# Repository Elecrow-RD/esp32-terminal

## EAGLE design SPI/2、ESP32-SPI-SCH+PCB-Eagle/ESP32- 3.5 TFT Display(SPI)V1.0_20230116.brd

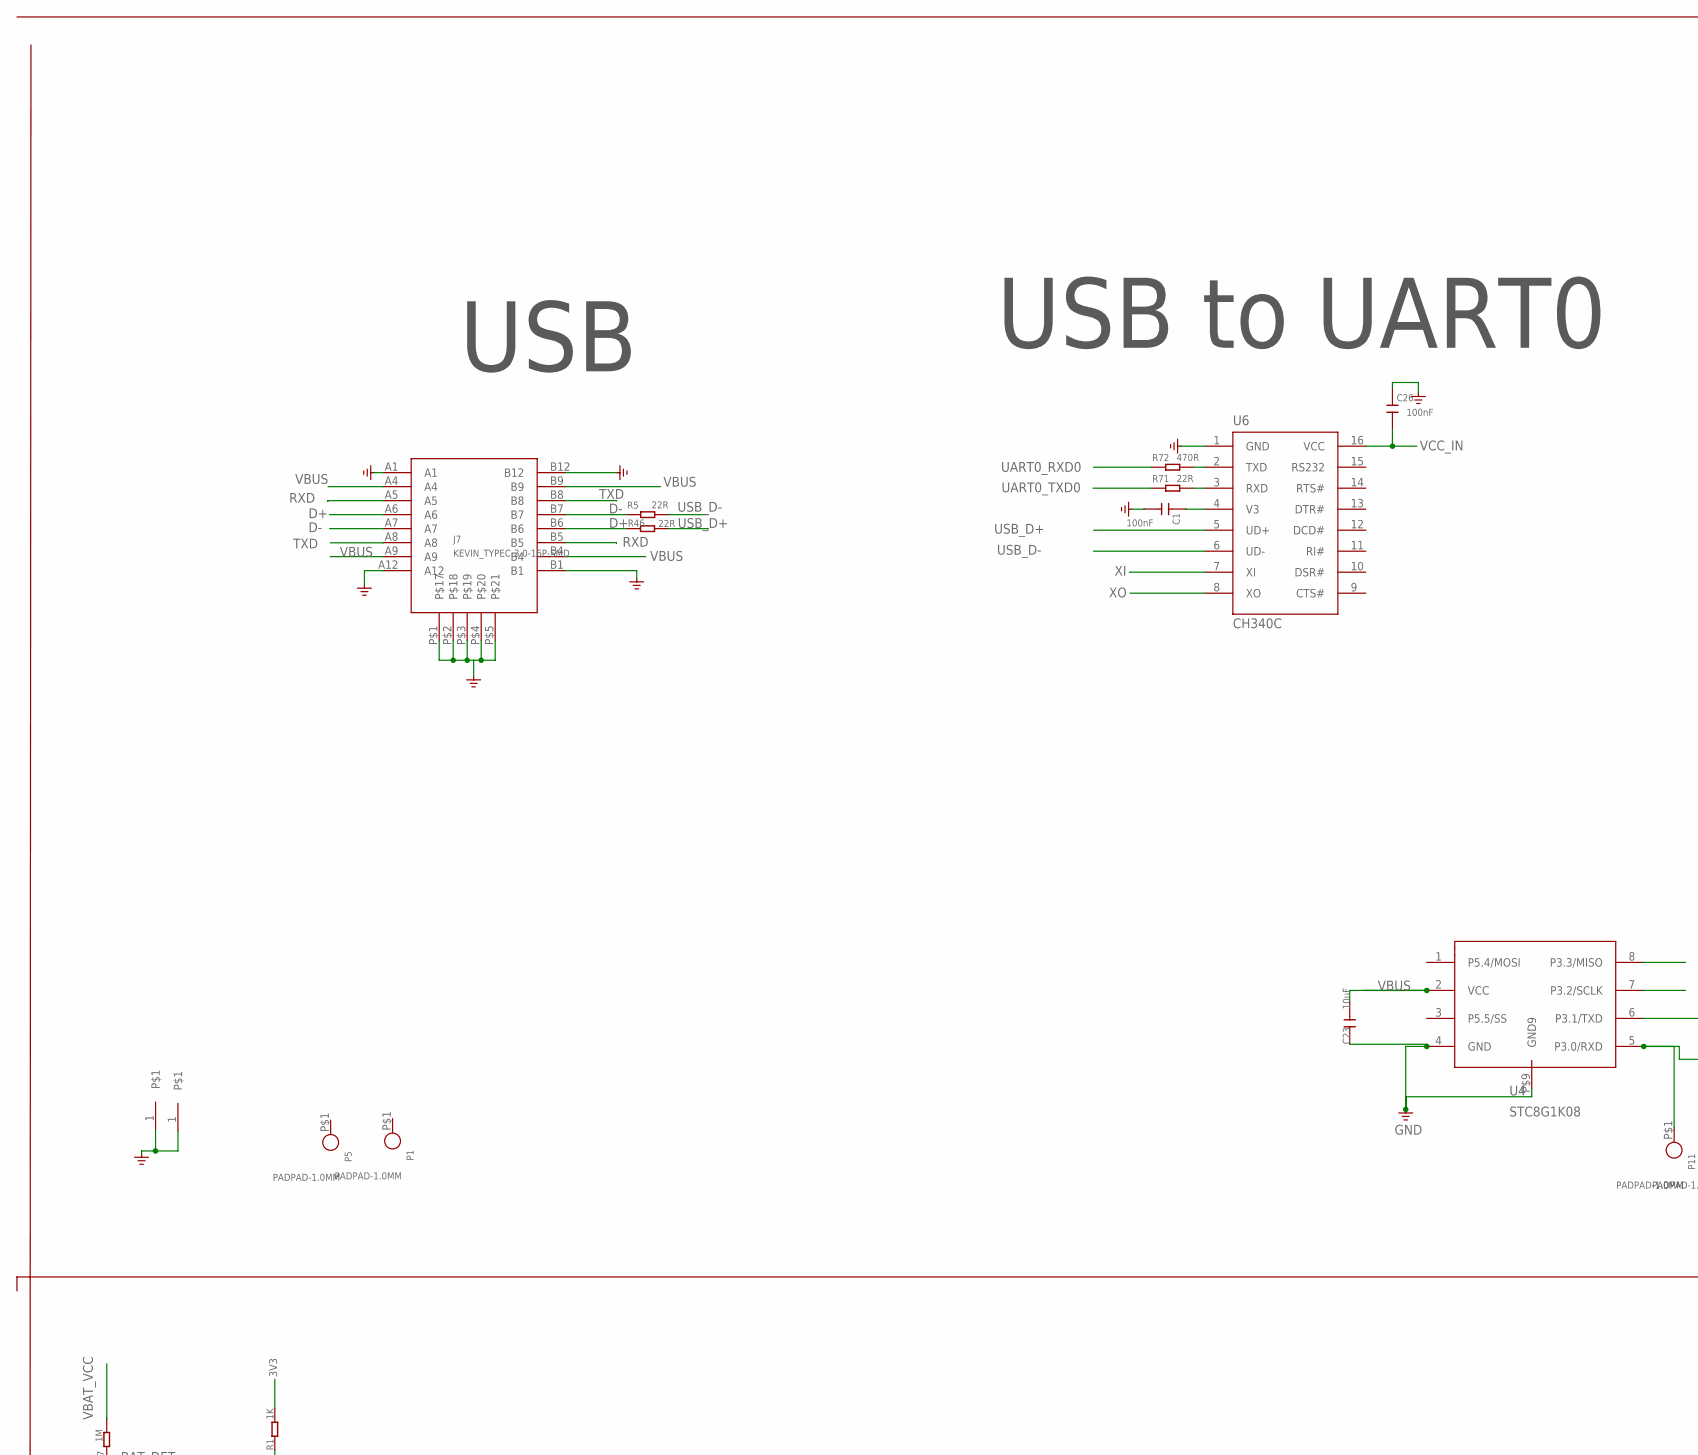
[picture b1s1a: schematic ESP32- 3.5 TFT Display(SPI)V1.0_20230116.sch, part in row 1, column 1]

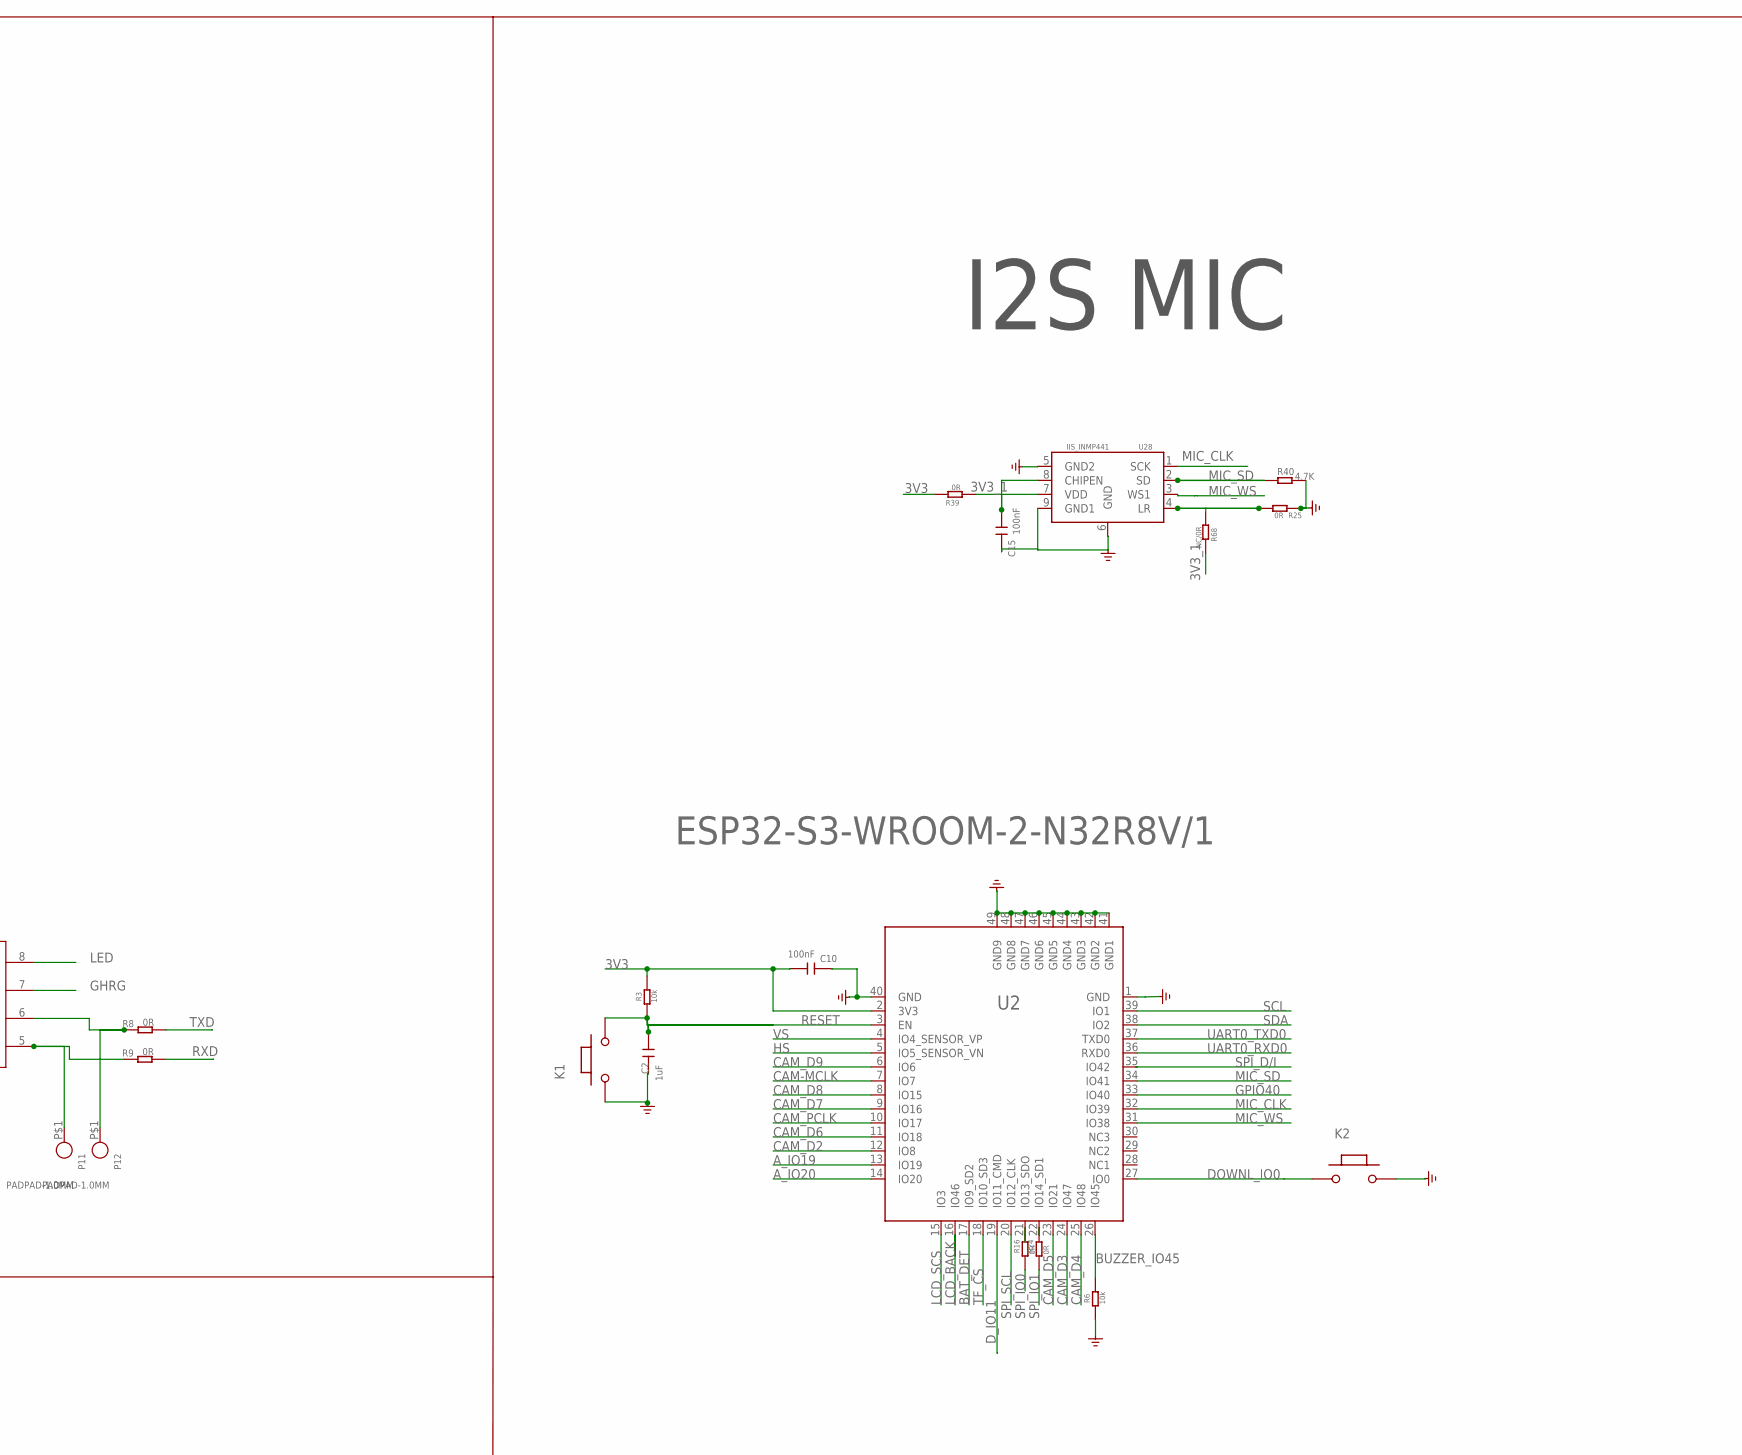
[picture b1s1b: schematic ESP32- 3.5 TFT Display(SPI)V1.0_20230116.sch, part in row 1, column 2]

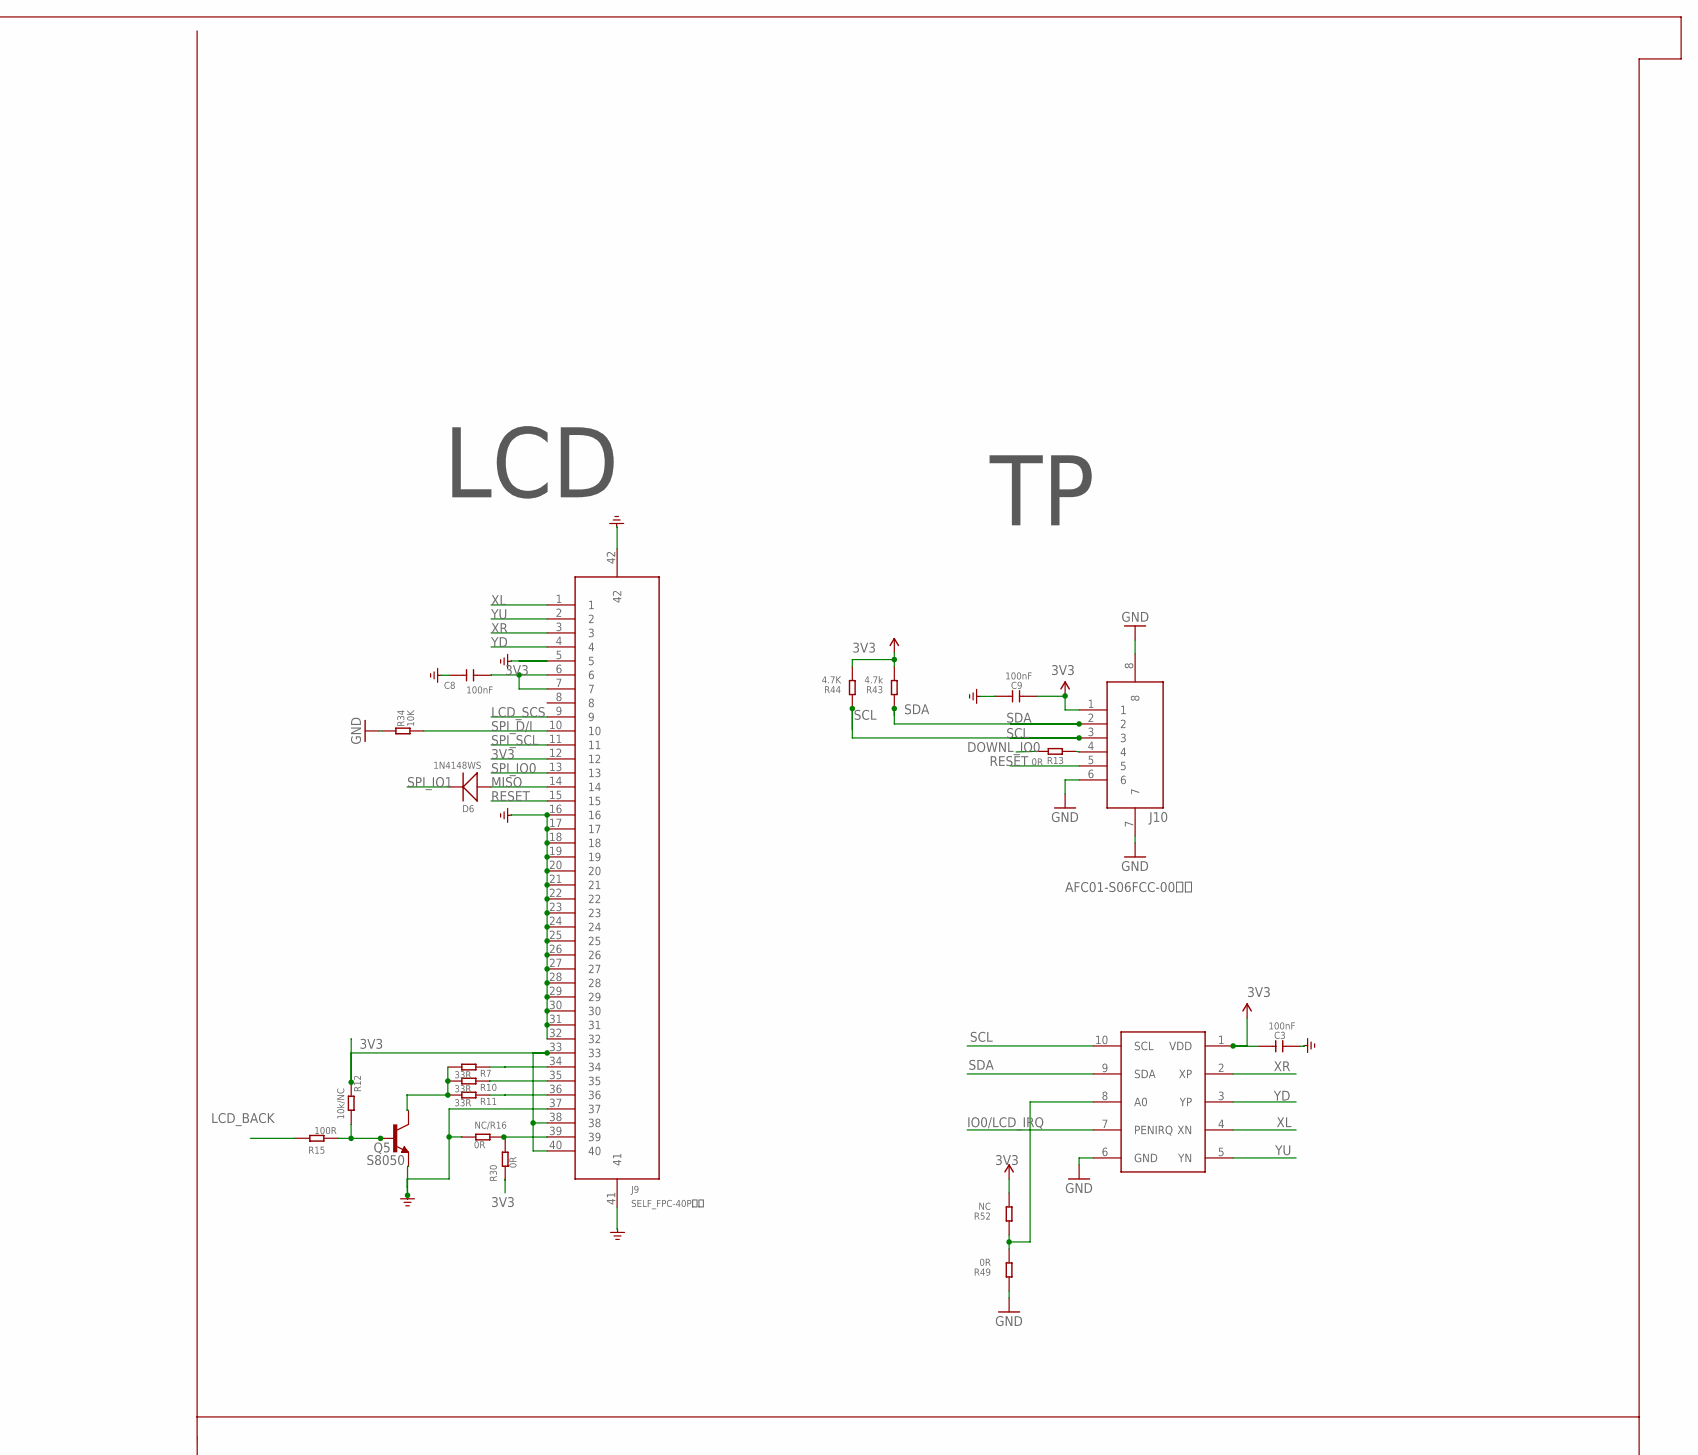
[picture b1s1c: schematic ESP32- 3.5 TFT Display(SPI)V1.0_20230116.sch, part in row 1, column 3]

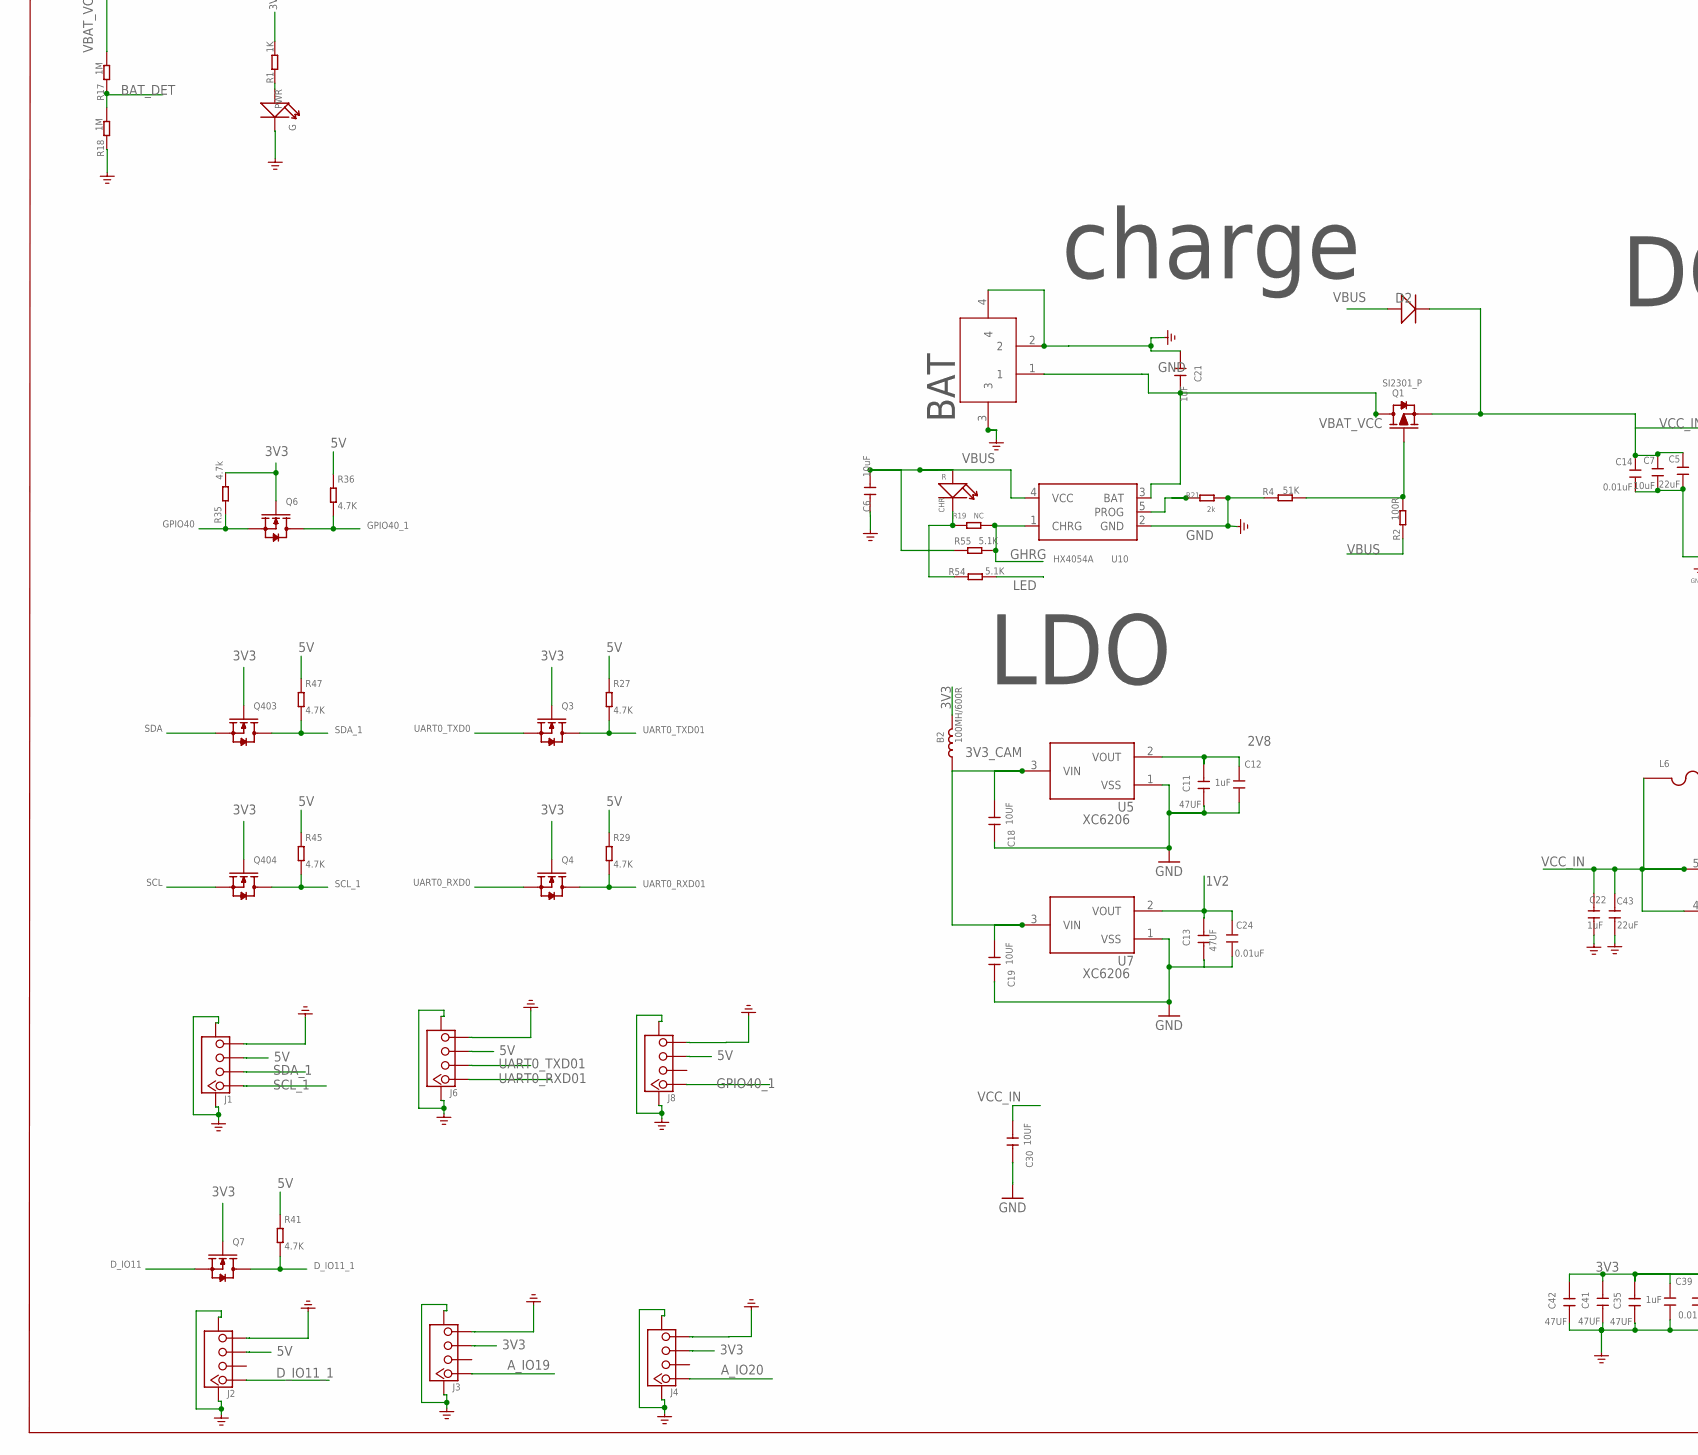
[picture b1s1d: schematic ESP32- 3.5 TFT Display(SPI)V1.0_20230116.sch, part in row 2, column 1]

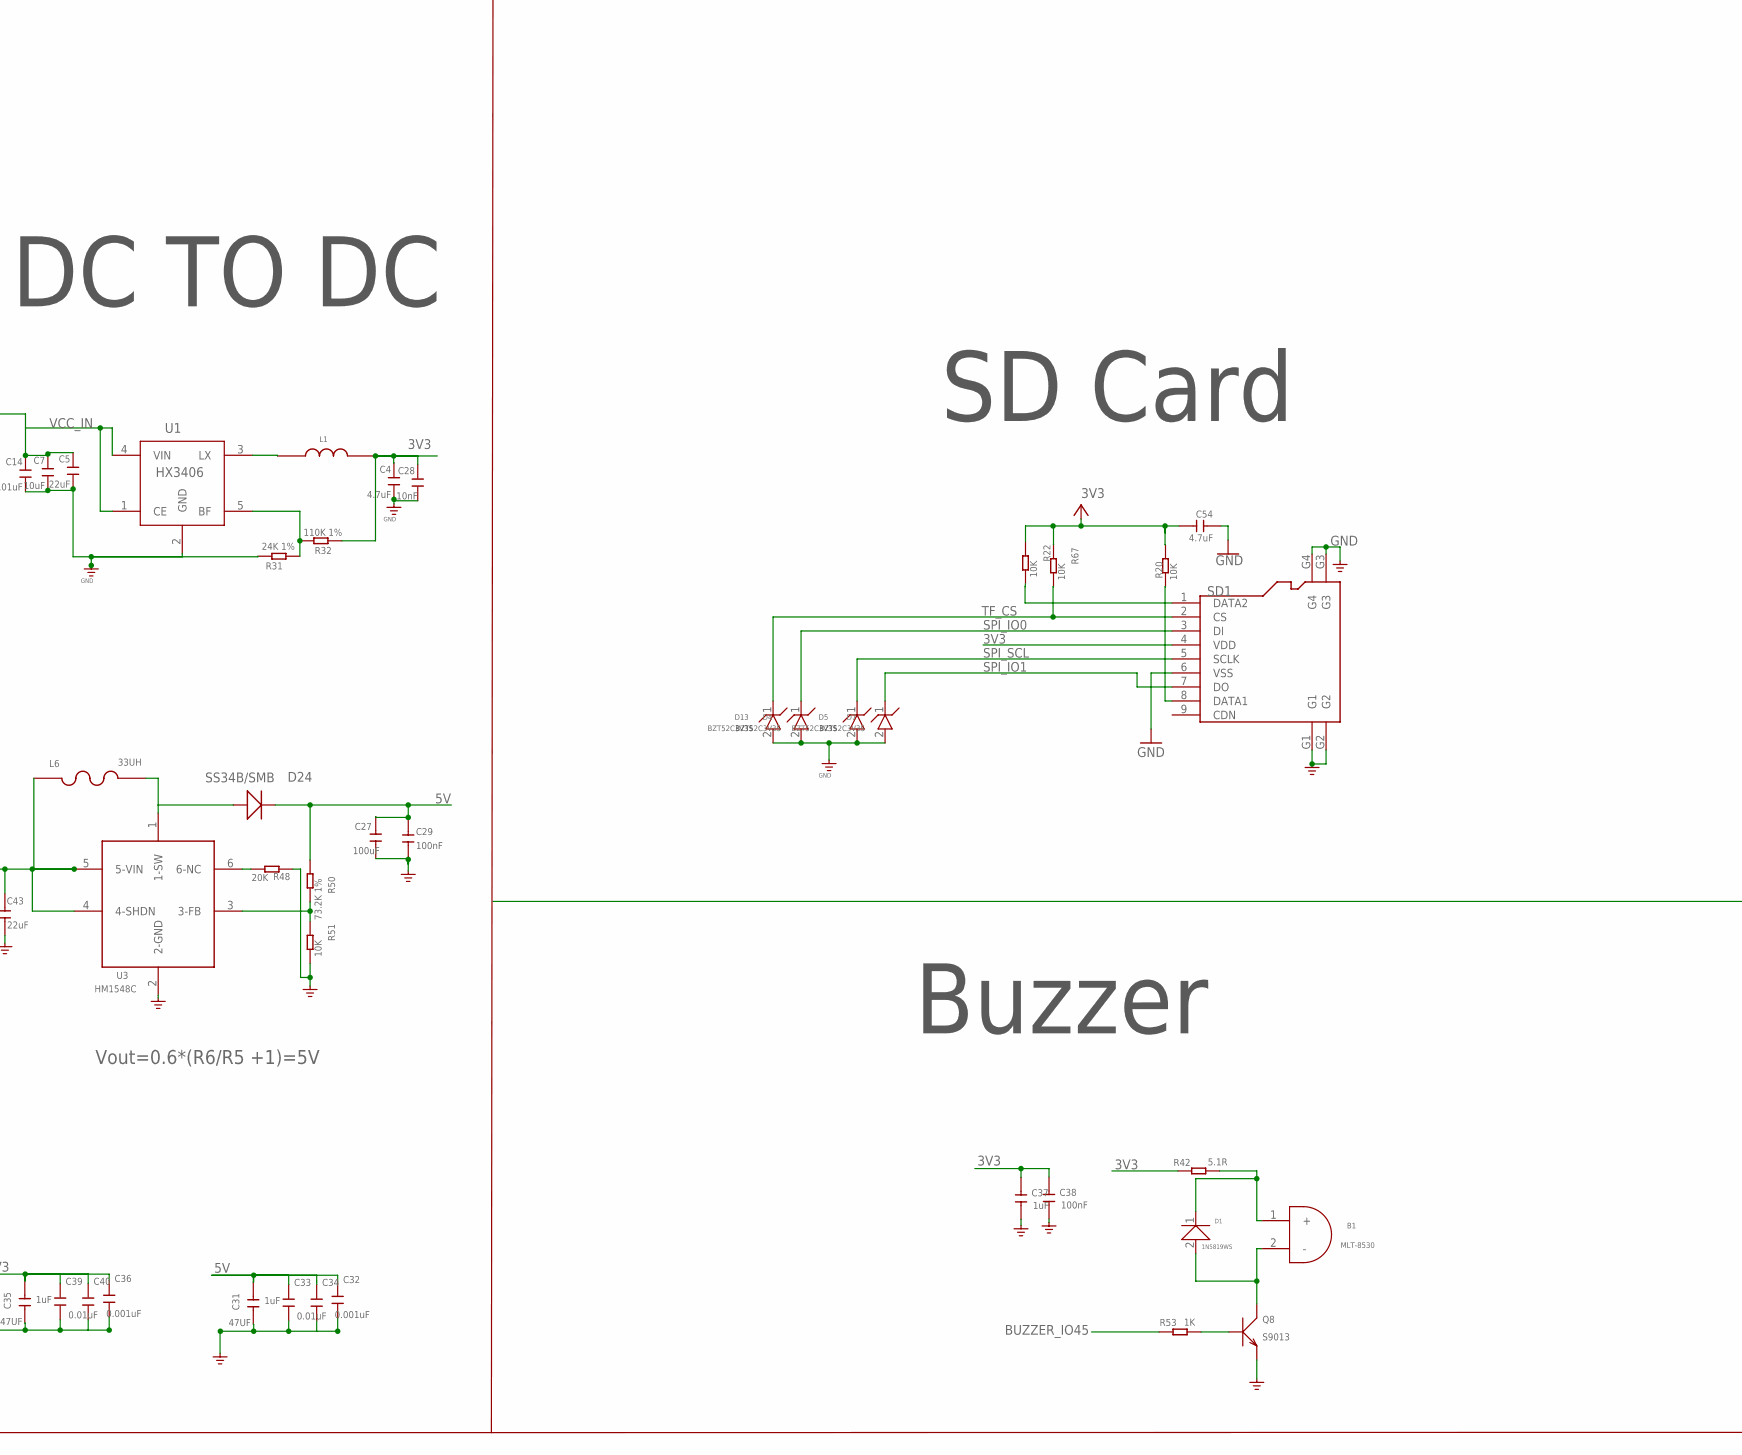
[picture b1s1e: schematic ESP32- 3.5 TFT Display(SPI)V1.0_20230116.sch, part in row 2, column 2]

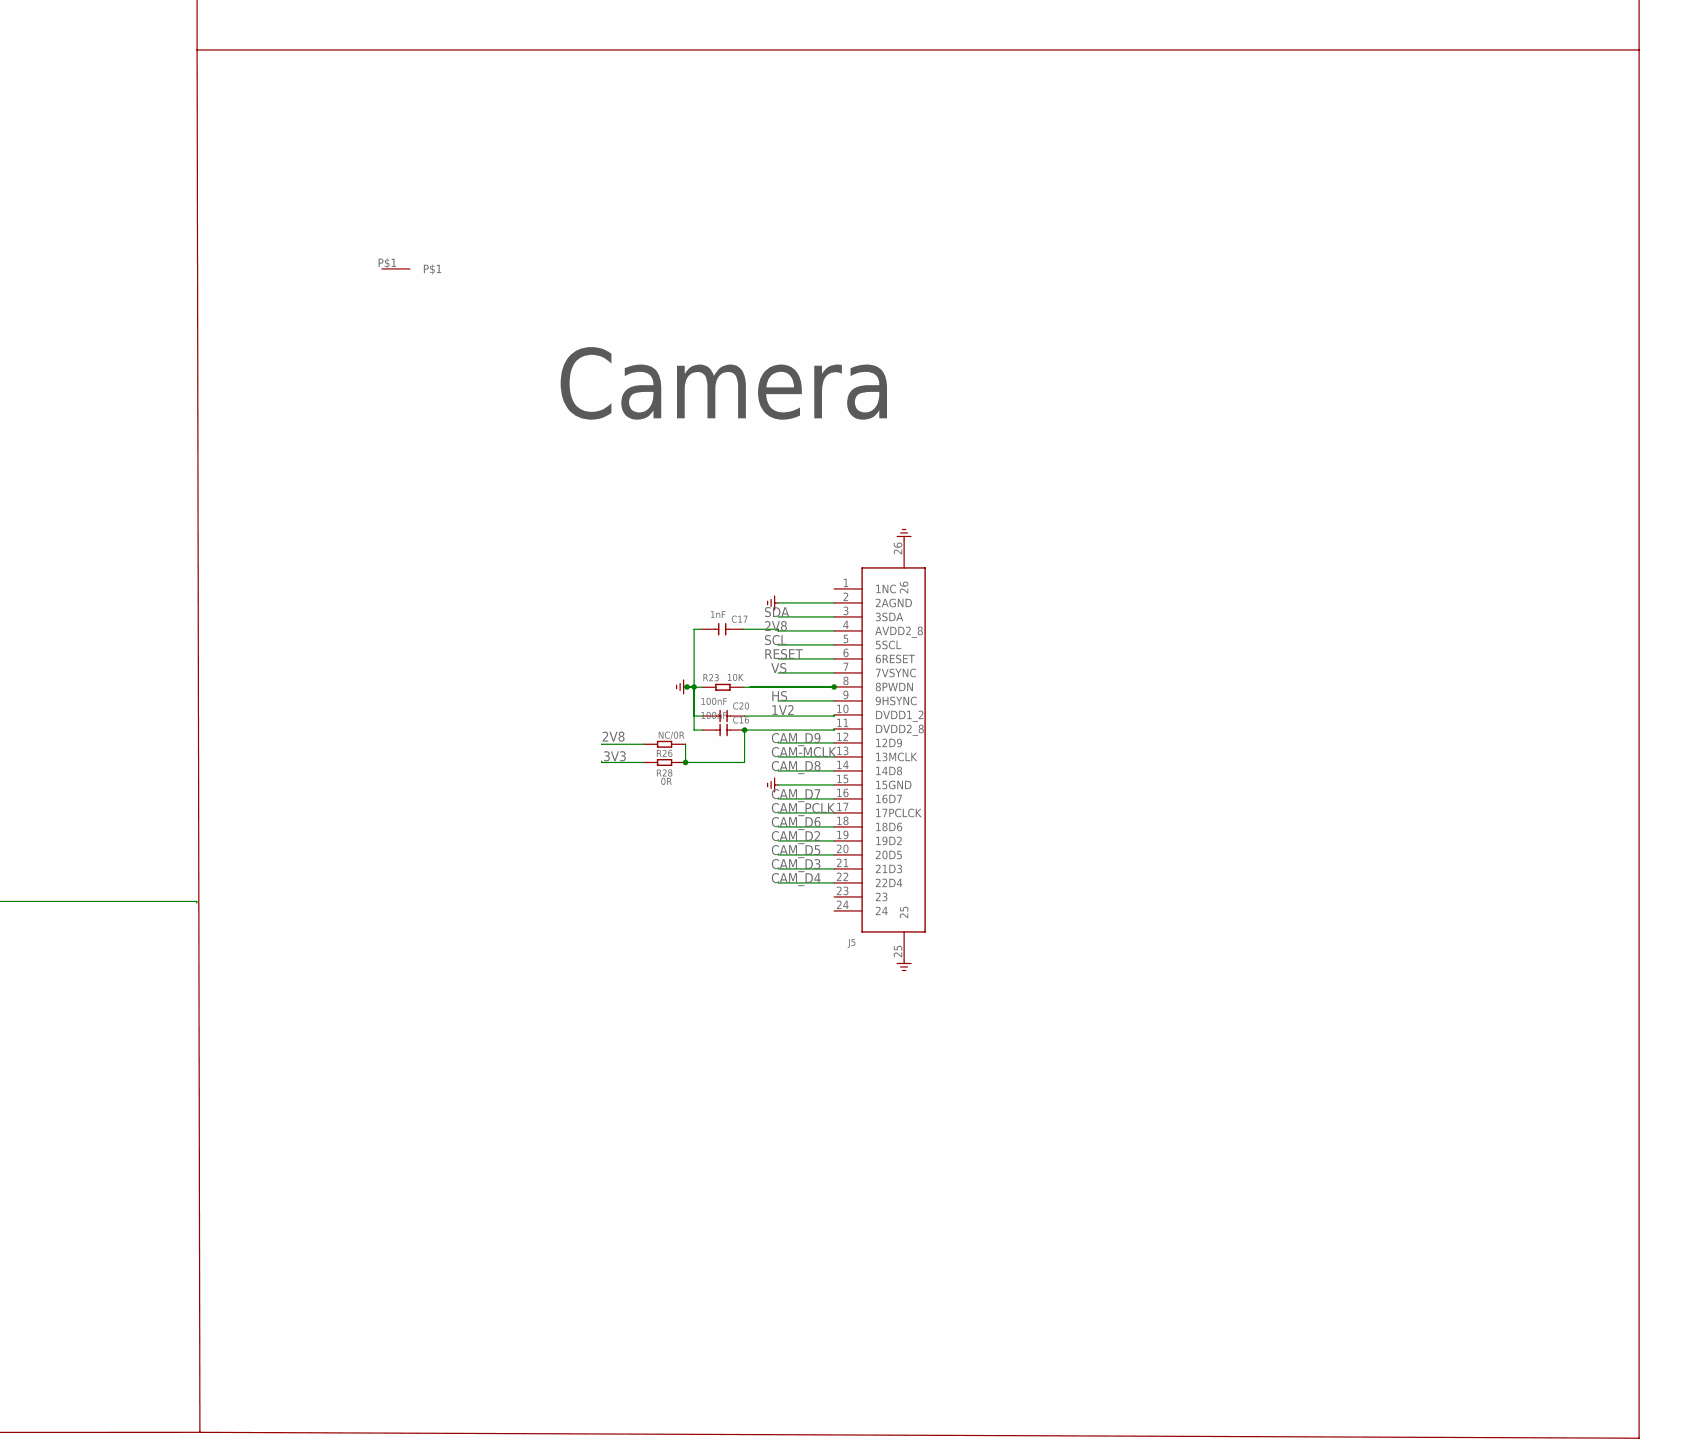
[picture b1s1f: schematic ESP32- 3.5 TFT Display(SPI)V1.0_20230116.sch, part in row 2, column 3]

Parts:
B1: MLT-8530
B2: 100MH/600R; 0805@1
BAT: CON-80-2P-M; 2P-2.0-M
C1, C26, C29: 100nF; 0603
C2, C21: 1uF; C0603
C3, C8, C9, C10, C15, C16, C20: 100nF; C0603
C4: 4.7uF; 0603
C5: 22uF; 0603
C6, C23: 10uF; C0603
C7: 10uF; 0603
C11, C13, C31, C35, C41, C42: 47UF; 1206
C12, C22, C33, C39: 1uF; 0603
C14, C24, C34, C40: 0.01uF; 0603
C17: 1nF; C0603
C18, C19, C30: 10UF; C0603
C27: 100uF; 0805
C28: 10nF; 0603
C32, C36: 0.001uF; 0603
C37: 1uF; DISCRETE_C0603
C38: 100nF; DISCRETE_C0603
C43: 22uF; 0805
C54: 4.7uF; DISCRETE_C0603
CHR: R; D0603
D1: 1N5819WS; SOD-323
D2: 1N5819/S0D-123; 1206-1
D4, D5, D7, D13: BZT52C3V3S; SOD-323@1
D6: 1N4148WS; SOD323
D24: SS34B/SMB; 214AB
J1, J2, J3, J4, J6, J8: TWIG-4P-2.0-SMD-FEMALE-REINFORCE'90D'; 4P-SMD-2.0-90D
J5: SMD_HEADERP_24PX0.5上接; SMD_HEADERP_24PX0.5
J7: KEVIN_TYPEC-3.0-16P-SMD; KEVIN_3.0TYPEC-SMD
J9: SELF_FPC-40P上接; SELF_SMD42-50P-2560L490W
J10: AFC01-S06FCC-00下接; SMD8-50P-740L535W
K1, K2: BUTTON; 157SW
L1: CD32_10uH; CD32
L6: 33UH; L773
NC/R16: 0R; R0603
P1, P5, P11, P12: PADPAD-1.0MM; PAD-1.0MM
P3, P4: 3M-5
PWR: G; LED-0603
Q1: SI2301_P; DISCRETE_SOT23
Q3, Q4, Q6, Q7, Q403, Q404: MOSFET-N'SOT23'; SOT23
Q5: S8050; SPARKFUN_SOT23
Q8: S9013; SOT23@1
R1: 1K; R0603
R2, R15: 100R; R0603
R3, R6: 10k; R0603
R4: 51K; R0603
R5, R46, R71: 22R; DISCRETE_R0603
R7, R10, R11: 33R; R0603
R8, R9, R16, R24, R25, R28, R30, R39: 0R; R0603
R12: 10k/NC; R0603
R13, R49: 0R; DISCRETE_R0603
R17, R18: 1M; R0603
R19: NC; R0603
R20, R22, R23, R34, R51, R67: 10K; DISCRETE_R0603
R21: 2k; R0603
R26, R68: NC/0R; R0603
R27, R29, R36, R41, R45, R47: 4.7K; R0603
R31: 24K 1%; R0603
R32: 110K 1%; R0603
R35: 4.7k; R0603
R40, R44: 4.7K; DISCRETE_R0603
R42: 5.1R; R0603
R43: 4.7k; DISCRETE_R0603
R48: 20K; DISCRETE_R0603
R50: 73.2K 1%; DISCRETE_R0603
R52: NC; DISCRETE_R0603
R53: 1K; DISCRETE_R0603
R54, R55: 5.1K; DISCRETE_R0603
R72: 470R; DISCRETE_R0603
SD1: HOLDER-MICROSD-9P; 9P-SMD-W/-RING
U1: HX3406; SOT23-5
U2: ESP32-S3-WROOM-2-N32R8V/1
U3: HM1548C; A_XBJ_SOT23-6
U4: STC8G1K08; DFN8
U5, U7: XC6206; SOT-23
U6: CH340C; SOP-16
U8: NS2009; MSOP10
U10: HX4054A; HX4054A_SOT23_5
U28: IIS_INMP441
U$63: TFT-3.5; LCD3.5寸

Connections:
1V2: C13.2, C20.1, C24.1, J5.10 (DVDD1_2), U7.2 (VOUT)
2V8: C11.2, C12.1, C17.1, J5.4 (AVDD2_8), R26.2, U5.2 (VOUT)
3V3: B2.2, C3.1, C4.1, C8.2, C9.2, C10.2, C28.1, C35.2, C36.1, C37.2, C38.2, C39.1, C40.1, C41.2, C42.2, C54.2, J3.3, J4.3, J9.6, J9.7, J9.12, J9.33, J9.38, J9.40, J10.1, L1.2, Q3.1 (G), Q4.1 (G), Q6.1 (G), Q7.1 (G), Q403.1 (G), Q404.1 (G), R1.2, R3.2, R12.2, R20.1, R22.1, R28.2, R30.1, R32.2, R35.2, R39.2, R42.1, R43.2, R44.2, R52.2, R67.1, SD1.4 (VDD), U2.2 (3V3), U8.1 (VDD)
3V3_1: C15.2, R39.1, R68.2, U28.7 (VDD), U28.8 (CHIPEN)
3V3_CAM: B2.1, C18.2, C19.2, U5.3 (VIN), U7.3 (VIN)
5V: C27.2, C29.2, C31.2, C32.1, C33.1, C34.1, D24.2 (-), J1.3, J2.3, J6.3, J8.3, R27.1, R29.1, R36.1, R41.1, R45.1, R47.1, R50.1
A_IO19: J3.1, U2.13 (IO19)
A_IO20: J4.1, U2.14 (IO20)
BAT_DET: R17.2, R18.1, U2.17 (IO9_SD2)
BUZZER_IO45: R6.2, R53.1, U2.26 (IO45)
CAM-MCLK: J5.13 (13MCLK), U2.7 (IO7)
CAM_D2: J5.19 (19D2), U2.12 (IO8)
CAM_D3: J5.21 (21D3), U2.24 (IO47)
CAM_D4: J5.22 (22D4), U2.25 (IO48)
CAM_D5: J5.20 (20D5), U2.23 (IO21)
CAM_D6: J5.18 (18D6), U2.11 (IO18)
CAM_D7: J5.16 (16D7), U2.9 (IO16)
CAM_D8: J5.14 (14D8), U2.8 (IO15)
CAM_D9: J5.12 (12D9), U2.6 (IO6)
CAM_PCLK: J5.17 (17PCLCK), U2.10 (IO17)
D+: J7.A6, J7.B6, R46.1
D-: J7.A7, J7.B7, R5.1
DOWNL_IO0: K2.1, R13.2, U2.27 (IO0)
D_IO11: Q7.2 (S), U2.19 (IO11_CMD)
D_IO11_1: J2.1, Q7.3 (D), R41.2
GHRG: R19.2, R55.2, U4.7 (P3.2/SCLK), U10.1 (CHRG)
GND: BAT.2, BAT.3, BAT.4, C1.1, C2.1, C3.2, C4.2, C5.2, C6.1, C7.2, C8.1, C9.1, C10.1, C11.1, C12.2, C13.1, C14.2, C15.1, C16.2, C17.2, C18.1, C19.1, C20.2, C21.1, C22.1, C23.1, C24.2, C26.2, C27.1, C28.2, C29.1, C30.1, C31.1, C32.2, C33.2, C34.2, C35.1, C36.2, C37.1, C38.1, C39.2, C40.2, C41.1, C42.1, C43.1, C54.1, D4.2, D5.2, D7.2, D13.2, J1.4, J1.SS1, J1.SS2, J2.4, J2.SS1, J2.SS2, J3.4, J3.SS1, J3.SS2, J4.4, J4.SS1, J4.SS2, J5.2 (2AGND), J5.15 (15GND), J5.25, J5.26, J6.4, J6.SS1, J6.SS2, J7.A1, J7.A12, J7.B1, J7.B12, J7.P$1, J7.P$2, J7.P$3, J7.P$4, J7.P$5, J8.4, J8.SS1, J8.SS2, J9.5, J9.16, J9.17, J9.18, J9.19, J9.20, J9.21, J9.22, J9.23, J9.24, J9.25, J9.26, J9.27, J9.28, J9.29, J9.30, J9.31, J9.32, J9.37, J9.41, J9.42, J10.6, J10.7, J10.8, K1.1, K2.2, NC/R16.1, P3.1, P4.1, PWR.-, Q5.2 (E), Q8.2 (E), R4.2, R6.1, R18.2, R21.2, R23.1, R25.2, R31.1, R34.1, R40.2, R48.1, R49.1, R51.2, SD1.6 (VSS), SD1.G1, SD1.G2, SD1.G3, SD1.G4, U1.2 (GND), U2.1 (GND), U2.40 (GND), U2.41 (GND1), U2.42 (GND2), U2.43 (GND3), U2.44 (GND4), U2.45 (GND5), U2.46 (GND6), U2.47 (GND7), U2.48 (GND8), U2.49 (GND9), U3.2 (2-GND), U4.4 (GND), U4.P$9 (GND9), U5.1 (VSS), U6.1 (GND), U7.1 (VSS), U8.6 (GND), U10.2 (GND), U28.5 (GND2), U28.6 (GND), U28.9 (GND1)
GPIO40: Q6.2 (S), R35.1, U2.33 (IO40)
GPIO40_1: J8.1, Q6.3 (D), R36.2
HS: J5.9 (9HSYNC), U2.5 (IO5_SENSOR_VN)
IO0/LCD_IRQ: U8.7 (PENIRQ)
LCD_BACK: R15.2, U2.16 (IO46)
LCD_SCS: J9.9, U2.15 (IO3)
LED: R54.2, U4.8 (P3.3/MISO)
MIC_CLK: U2.32 (IO39), U28.1 (SCK)
MIC_SD: R40.1, U2.34 (IO41), U28.2 (SD)
MIC_WS: U2.31 (IO38), U28.3 (WS1)
MISO: D6.+, J9.14
unnamed: C1.2, U6.4 (V3)
unnamed: PWR.+, R1.1
unnamed: CHR.-, R19.1, R54.1
unnamed: Q1.1 (G), R2.1, R4.1
unnamed: P12.P$1, R8.2, U4.6 (P3.1/TXD)
unnamed: P11.P$1, R9.2, U4.5 (P3.0/RXD)
unnamed: D24.1 (+), L6.2, U3.1 (1-SW)
unnamed: J9.34, R7.2
unnamed: L1.1, U1.3 (LX)
unnamed: J9.35, R10.2
unnamed: C16.1, J5.11 (DVDD2_8), R26.1, R28.1
unnamed: J9.36, R11.2
unnamed: Q5.3 (C), R7.1, R10.1, R11.1
unnamed: Q5.1 (B), R12.1, R15.1
unnamed: J9.39, NC/R16.2, R30.2
unnamed: R24.2, U2.22 (IO14_SD1)
unnamed: R16.2, U2.21 (IO13_SDO)
unnamed: R25.1, R68.1, U28.4 (LR)
unnamed: J10.4, R13.1
unnamed: R31.2, R32.1, U1.5 (BF)
unnamed: R48.2, U3.6 (6-NC)
unnamed: J5.8 (8PWDN), R23.2
unnamed: R49.2, R52.1, U8.8 (A0)
unnamed: B1.2 (-), D1.2 (+), Q8.3 (C)
unnamed: B1.1 (+), D1.1 (-), R42.2
unnamed: R50.2, R51.1, U3.3 (3-FB)
unnamed: R21.1, U10.5 (PROG)
unnamed: Q8.1 (B), R53.2
unnamed: R72.2, U6.2 (TXD)
unnamed: R71.2, U6.3 (RXD)
unnamed: R22.2, SD1.1 (DATA2)
unnamed: R20.2, SD1.8 (DATA1)
RESET: C2.2, J5.6 (6RESET), J9.15, J10.5, K1.2, R3.1, U2.3 (EN)
RXD: J7.A5, J7.B5, R9.1
SCL: J5.5 (5SCL), J10.3, Q404.2 (S), R44.1, U2.39 (IO1), U8.10 (SCL)
SCL_1: J1.1, Q404.3 (D), R45.2
SDA: J5.3 (3SDA), J10.2, Q403.2 (S), R43.1, U2.38 (IO2), U8.9 (SDA)
SDA_1: J1.2, Q403.3 (D), R47.2
SPI_D/I: J9.10, R34.2, U2.35 (IO42)
SPI_IO0: D4.1, J9.13, R16.1, SD1.3 (DI)
SPI_IO1: D6.-, D7.1, R24.1, SD1.7 (DO)
SPI_SCL: D5.1, J9.11, SD1.5 (SCLK), U2.20 (IO12_CLK)
TF_CS: D13.1, R67.2, SD1.2 (CS), U2.18 (IO10_SD3)
TXD: J7.A8, J7.B8, R8.1
UART0_RXD0: Q4.2 (S), R72.1, U2.36 (RXD0)
UART0_RXD01: J6.1, Q4.3 (D), R29.2
UART0_TXD0: Q3.2 (S), R71.1, U2.37 (TXD0)
UART0_TXD01: J6.2, Q3.3 (D), R27.2
USB_D+: R46.2, U6.5 (UD+)
USB_D-: R5.2, U6.6 (UD-)
VBAT_VCC: BAT.1, C21.2, Q1.3 (D), R17.1, U10.3 (BAT)
VBUS: C6.2, C23.2, CHR.+, D2.A (+), J7.A4, J7.A9, J7.B4, J7.B9, R2.2, R55.1, U4.2 (VCC), U10.4 (VCC)
VCC_IN: C5.1, C7.1, C14.1, C22.2, C26.1, C30.2, C43.2, D2.C (-), L6.1, Q1.2 (S), U1.1 (CE), U1.4 (VIN), U3.4 (4-SHDN), U3.5 (5-VIN), U6.16 (VCC)
VS: J5.7 (7VSYNC), U2.4 (IO4_SENSOR_VP)
XI: U6.7 (XI)
XL: J9.1, U8.4 (XN)
XO: U6.8 (XO)
XR: J9.3, U8.2 (XP)
YD: J9.4, U8.3 (YP)
YU: J9.2, U8.5 (YN)

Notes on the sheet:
USB
USB to UART0
charge
LCD
SD Card
DC TO DC
Camera
I2S MIC
LDO
Vout=0.6*(R6/R5 +1)=5V
BAT
Buzzer

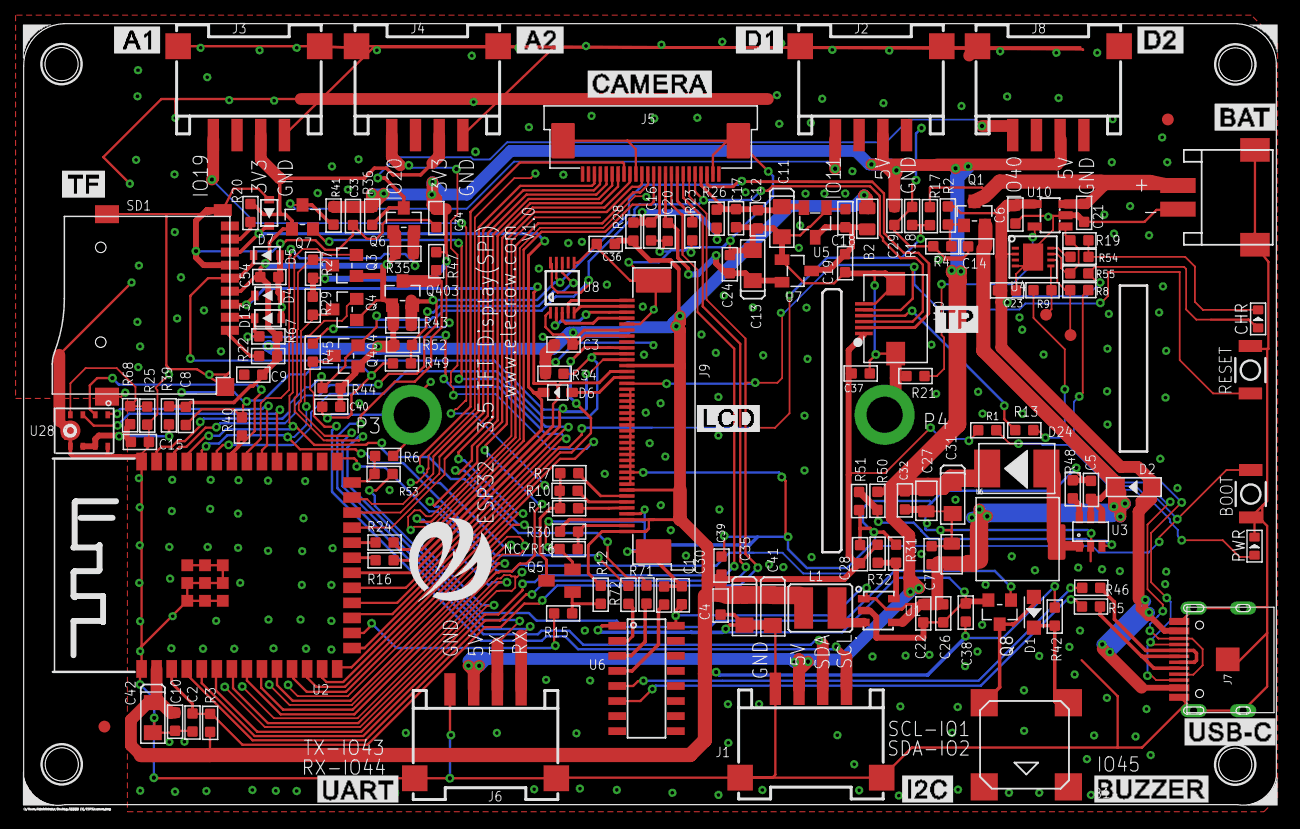
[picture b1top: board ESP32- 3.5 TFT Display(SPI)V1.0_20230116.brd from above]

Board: 2 copper layers, 105.7 x 66.0 mm, 156 parts (1 on the bottom side), 95 nets.

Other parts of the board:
U$24: ESP32-SPI2
U$42: LOGO
U$44: TOP-SMT-ESP32

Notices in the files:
parts and their libraries:
SparkFun-PowerSymbols: Licensing: Creative Commons ShareAlike 4.0 International - https://creativecommons.org/licenses/by-sa/4.0
